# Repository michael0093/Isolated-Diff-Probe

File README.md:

# Overview
The Ti AMC33xx are differential isolated analog amplifiers rated for minimum 1.2kVrms insulation. The AMC3302 is intended for current shunt inputs as it has a +/-50mVpp input with a fixed gain of 41, whereas the AMC3330 is better for voltage measurements as it has a +/-1Vpp input and a fixed gain of 2. In these probes the AMC33xx do all the work, with their differential output converted to single-ended by a dual op-amp to better suit most oscilloscopes. 
By using two 2.54" jumpers on the 2x10 header, you can select between various input attenuators for low to high voltage use. 

# Design Notes
The power supply must be isolated from your scope as the scope "GND" of the SMA connector is a 50%VDD bias voltage. 
The schematic has two modifications from the rev A to rev A2 design - refer to the rev B schematic and follow the notes. The modifications are:
- Two biasing 1M (AMC3300) or 100k (AMC3302) resistors from near the input selector to HGND
- Two filtering 33pF (AMC3300) or 3.3nF (AMC3302) capacitors from near the input selector to HGND
- General note: The PCB is marked with an fc of the input circuit, not of the complete probe. The fc of the complete probe is about 300kHz.

The design was originally done in Altium and then converted to KiCad so appologies that the KiCad sch/pcb may not link up quite right. For that reason there are no propper rev B output files, and also note the rev B PCB still has outstanding changes as noted on the schematic.

Other opamps with GBWP >1MHz or so should perform similarly, the OPA2376 is just what was on hand.
Based on practical usage, the AMC3302 with a 0R01 shunt works best for currents >=3mA with fc=100kHz. The AMC3330 on 1:1 range works best for voltages >=10mV and fc=300kHz.

# Disclaimer
Only use the high voltage inputs if you are suitably qualified to measure lethal voltages and completely understand the risks. This project is provided as reference material only and anyone who attempts to make it must fully understand the risks and limitations of the isolator used - this project has absolutely no warranty and may be completely unsuitable for your use case. Use completely at your own risk!

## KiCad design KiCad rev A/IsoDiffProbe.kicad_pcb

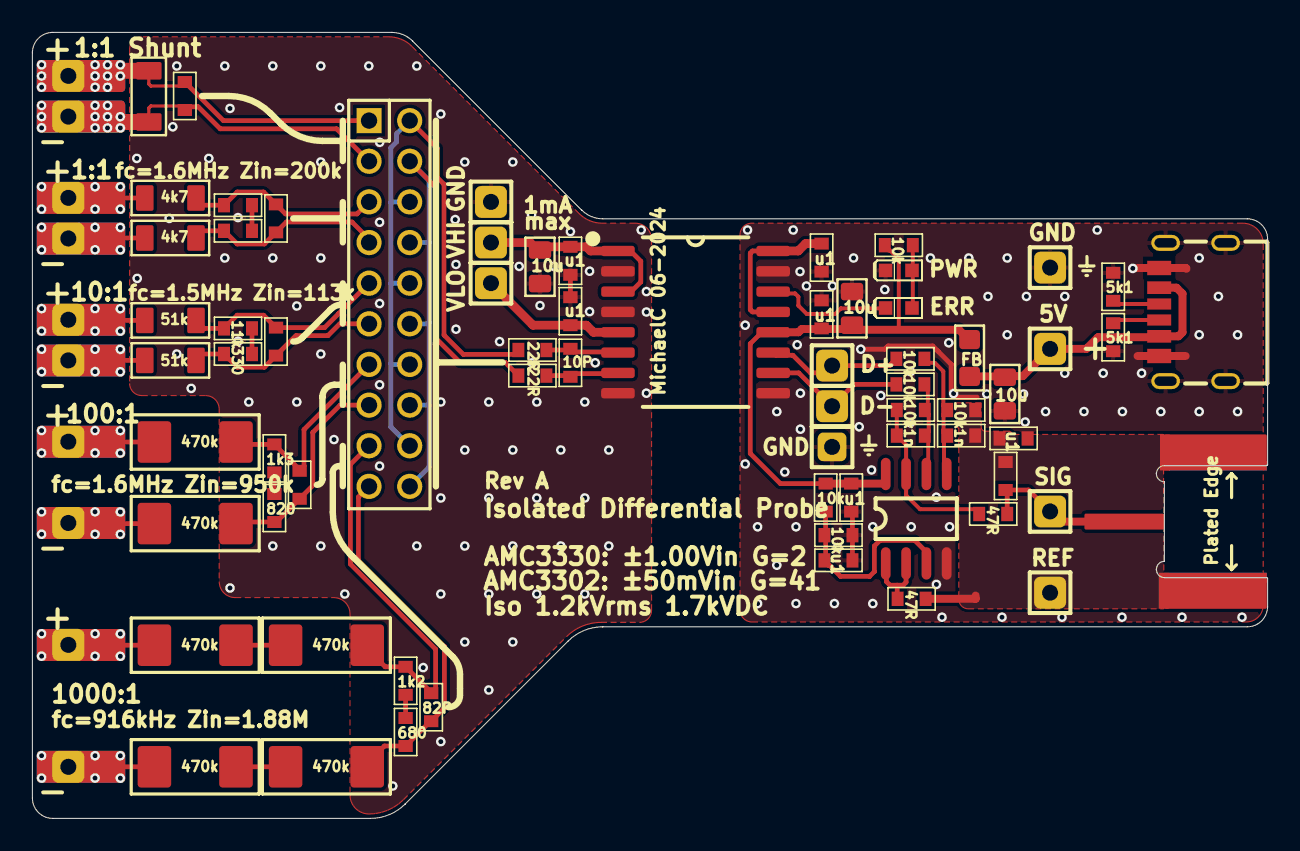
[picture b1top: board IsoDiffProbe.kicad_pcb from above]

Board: 2 copper layers, 77.2 x 49.1 mm, 79 parts (0 on the bottom side), 48 nets.

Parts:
C1, C2, C9, C13, C14: NF; 0603
C3, C5, C6, C10, C16, C17, C18: 100nF; 0603
C4, C7, C8: 10uF / 25V; 0805_cap_Rounded
C11: 10pF; 0603
C12, C15: 1nF; 0603
C19: 82pF; 0603
D1: RED; LED-0603
D2: GRN; LED-0603
J1: USB C 6-Pin; USB-C_6pin_Conn
J2: SMA Conn; SMA_SMD
L1: PBY201209T-601Y-N; 0805_Rounded
P1: Header 10X2; IDC20
R1: 0R01; 1206
R2, R6: 4k7; 1206
R3, R16, R17, R20, R21, R24, R29: 10k; 0603
R4, R5: NF; 0603
R7, R8: 5k1; 0603
R9, R14: 51k; 1206
R10: 11k; 0603
R11, R13: 220R; 0603
R12: 330R; 0603
R15, R23, R26, R27, R31, R32: 470k; MMB0207
R18, R25: 47R; 0603
R19: 1k3; 0603
R22: 820R; 0603
R28: 1k2; 0603
R30: 680R; 0603
TP1, TP2, TP3, TP4, TP5, TP6, TP7, TP8, TP9, TP10, TP11, TP12, TP13, TP14, TP15, TP16, TP17, TP18, TP19, TP20: Test Point; TP
U1: AMC3; DW0016B
U2: TLC272ID; SO-8

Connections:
+5V: C6.2, C7.1, C16.1, L1.1, R3.2, R24.1, U1.12, U2.8
GND: C3.1, C6.1, C7.2, C8.2, C16.2, C17.2, C18.2, D2.K, J1.A12, J1.B12, J1.G1, J1.G2, J1.G3, J1.G4, R7.1, R8.1, R29.2, TP7.1, TP19.1, U1.9, U1.15, U2.4
HGND: C4.1, C5.2, C10.2, TP18.1, U1.2, U1.4, U1.8
ISOLDO: C10.1, TP20.1, U1.5
ISOPWR: C4.2, C5.1, TP17.1, U1.1, U1.3
NetC1_1: C1.1, P1.1, R1.2, TP1.1
NetC1_2: C1.2, P1.3, R1.1, TP2.1
NetC2_1: C2.1, P1.5, R2.2, R4.1
NetC2_2: C2.2, P1.7, R5.2, R6.2
NetC3_2: C3.2, U1.13, U1.16
NetC9_1: C9.1, P1.9, R9.2, R10.1
NetC9_2: C9.2, P1.11, R12.2, R14.2
NetC11_1: C11.1, R11.1, U1.6
NetC11_2: C11.2, R13.1, U1.7
NetC12_1: C12.1, R16.1, R17.1, U2.6
NetC12_2: C12.2, R16.2, R18.2, U2.7
NetC13_1: C13.1, J2.FEED, R18.1, TP15.1
NetC14_1: C14.1, P1.13, R15.2, R19.1
NetC14_2: C14.2, P1.15, R22.2, R23.2
NetC15_1: C15.1, R20.1, R21.1, U2.5
NetC18_1: C18.1, R24.2, R29.1, U2.3
NetC19_1: C19.1, P1.17, R27.2, R28.1
NetC19_2: C19.2, P1.19, R30.2, R32.2
NetD1_A: D1.A, D2.A, R3.1
NetD1_K: D1.K, U1.14
NetJ1_A5: J1.A5, R7.2
NetJ1_B5: J1.B5, R8.2
NetP1_2: P1.2, P1.6, P1.10, P1.14, P1.18, R11.2
NetP1_4: P1.4, P1.8, P1.12, P1.16, P1.20, R13.2
NetR2_1: R2.1, TP3.1
NetR4_2: R4.2, R5.1
NetR6_1: R6.1, TP4.1
NetR9_1: R9.1, TP5.1
NetR10_2: R10.2, R12.1
NetR14_1: R14.1, TP8.1
NetR15_1: R15.1, TP9.1
NetR17_2: R17.2, TP13.1, U1.10
NetR19_2: R19.2, R22.1
NetR20_2: R20.2, TP14.1, U1.11
NetR23_1: R23.1, TP10.1
NetR25_2: R25.2, U2.1, U2.2
NetR26_1: R26.1, TP11.1
NetR26_2: R26.2, R27.1
NetR28_2: R28.2, R30.1
NetR31_1: R31.1, TP12.1
NetR31_2: R31.2, R32.1
VGND: C13.2, C15.2, C17.1, J2.GND, R21.2, R25.1, TP16.1
VIN: C8.1, J1.A9, J1.B9, L1.2, TP6.1

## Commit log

2024-11-05 Tidy up and add rev A0 files from local copy
2024-11-08 Clean Altium file. REv A1 mods
2024-11-09 Update readme and add bode plot
2024-11-12 Add rev B PCB that includes mods (still not linked to sch)
2024-11-12 Update gitignore to remove history zips
2025-08-10 Value changes to improve rev A1->A2 and updated rev B design.
